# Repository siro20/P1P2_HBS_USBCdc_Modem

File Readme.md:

# Daikin P1/P2 Raspberry Pi hat

This project is about a Raspberry Pi hat/standalone interface to communicate
over the proprietary Daikin P1/P2 power-line bus.

Instead of a [MAX22088](https://www.analog.com/en/products/max22088.html)
it uses a [Raspberry Pi Pico](https://www.raspberrypi.com/products/raspberry-pi-pico/)
and [LM4871](https://www.ti.com/product/LM4871) audio amplifier as modem.

For more details on P1/P2 bus check out
[https://github.com/Arnold-n/P1P2Serial](https://github.com/Arnold-n/P1P2Serial).

It features:
- Galvanic isolation
- 115200baud ASCII [UART interface](pico/doc/uart.md)
- [3 Status LEDs](pico/doc/leds.md)
- Autonomous mode to emulate "External controller" on address F0h
- Bus idle/busy detection
- Collision detection on TX
- Easy to solder: [no QFN parts, only SOIC-8](kicad/doc/circuits.md)
- Cost around 20€ (PCB + parts)
- Raspberry Pi hat compatible (powered from +5V)
- Micro-USB for standalone mode (powered over USB)

The board can be powered over Micro-USB only and doesn't need a Raspberry Pi
baseboard. The communication then will be done over the virtual USB UART.

    This project is not an offical Daikin product. Use own your own risk!
    It has been tested on a Daikin EJHA04AAV3.

## Chapters

- [User handbook](doc/handbook.md)
- [The electronics in detail](kicad/doc/circuits.md)
- [Ti LM4871 vs STM TS4990](kicad/doc/clicks.md)
- [Emulating a differential ADC](pico/doc/ADC.md)
- [Protocol used by the UART](pico/doc/uart.md)
- [Decoding the LED status](pico/doc/leds.md)
- [Hardware off-load the P1/P2 encoding using PIO0](pico/doc/Pio0.md)
- [Hardware off-load inversing ADC channel1](pico/doc/Pio1.md)

## Sources

- The hardware can be found here: [kicad](./kicad)
- The software can be found here: [pico](./pico)
- The host software can be found here: [siro20/P1P2decoder](https://github.com/siro20/P1P2decoder)

## The hardware

There are 3 connectors on the Pi hat:
1. Rasperry Pi 40-pin header
   - Provides power
   - Connects to the UART on GPIO14/GPIO15
   - Connects CTS/RTS on GPIO16/GPIO17
   - Signals a bus collision on GPIO22
2. P1/P2 bus connector
   - P1
   - P2
   - Earth
3. Micro USB
   - Allows to update the Pico firmware
   - Powers the board when used in standalone mode
   - Optional when using the 40-pin header

Buttons:
   - A. Reset button
   - B. Boot-mode button

      Hold button B and press button A to enter the Raspberry Pico USB bootloader.

## Disclaimer

    THE OPEN SOURCE SOFTWARE/HARDWARE IN THIS PROJECT IS DISTRIBUTED
    IN THE HOPE THAT IT WILL BE USEFUL, BUT WITHOUT ANY WARRANTY, WITHOUT
    EVEN THE IMPLIED WARRANTY OF MERCHANTABILITY OR FITNESS FOR A
    PARTICULAR PURPOSE.

    The "Daikin P1/P2 Raspberry Pi hat" has been designed and tested with
    Daikin's P1/P2 bus. You must not use this project to interface any
    other electrical bus.

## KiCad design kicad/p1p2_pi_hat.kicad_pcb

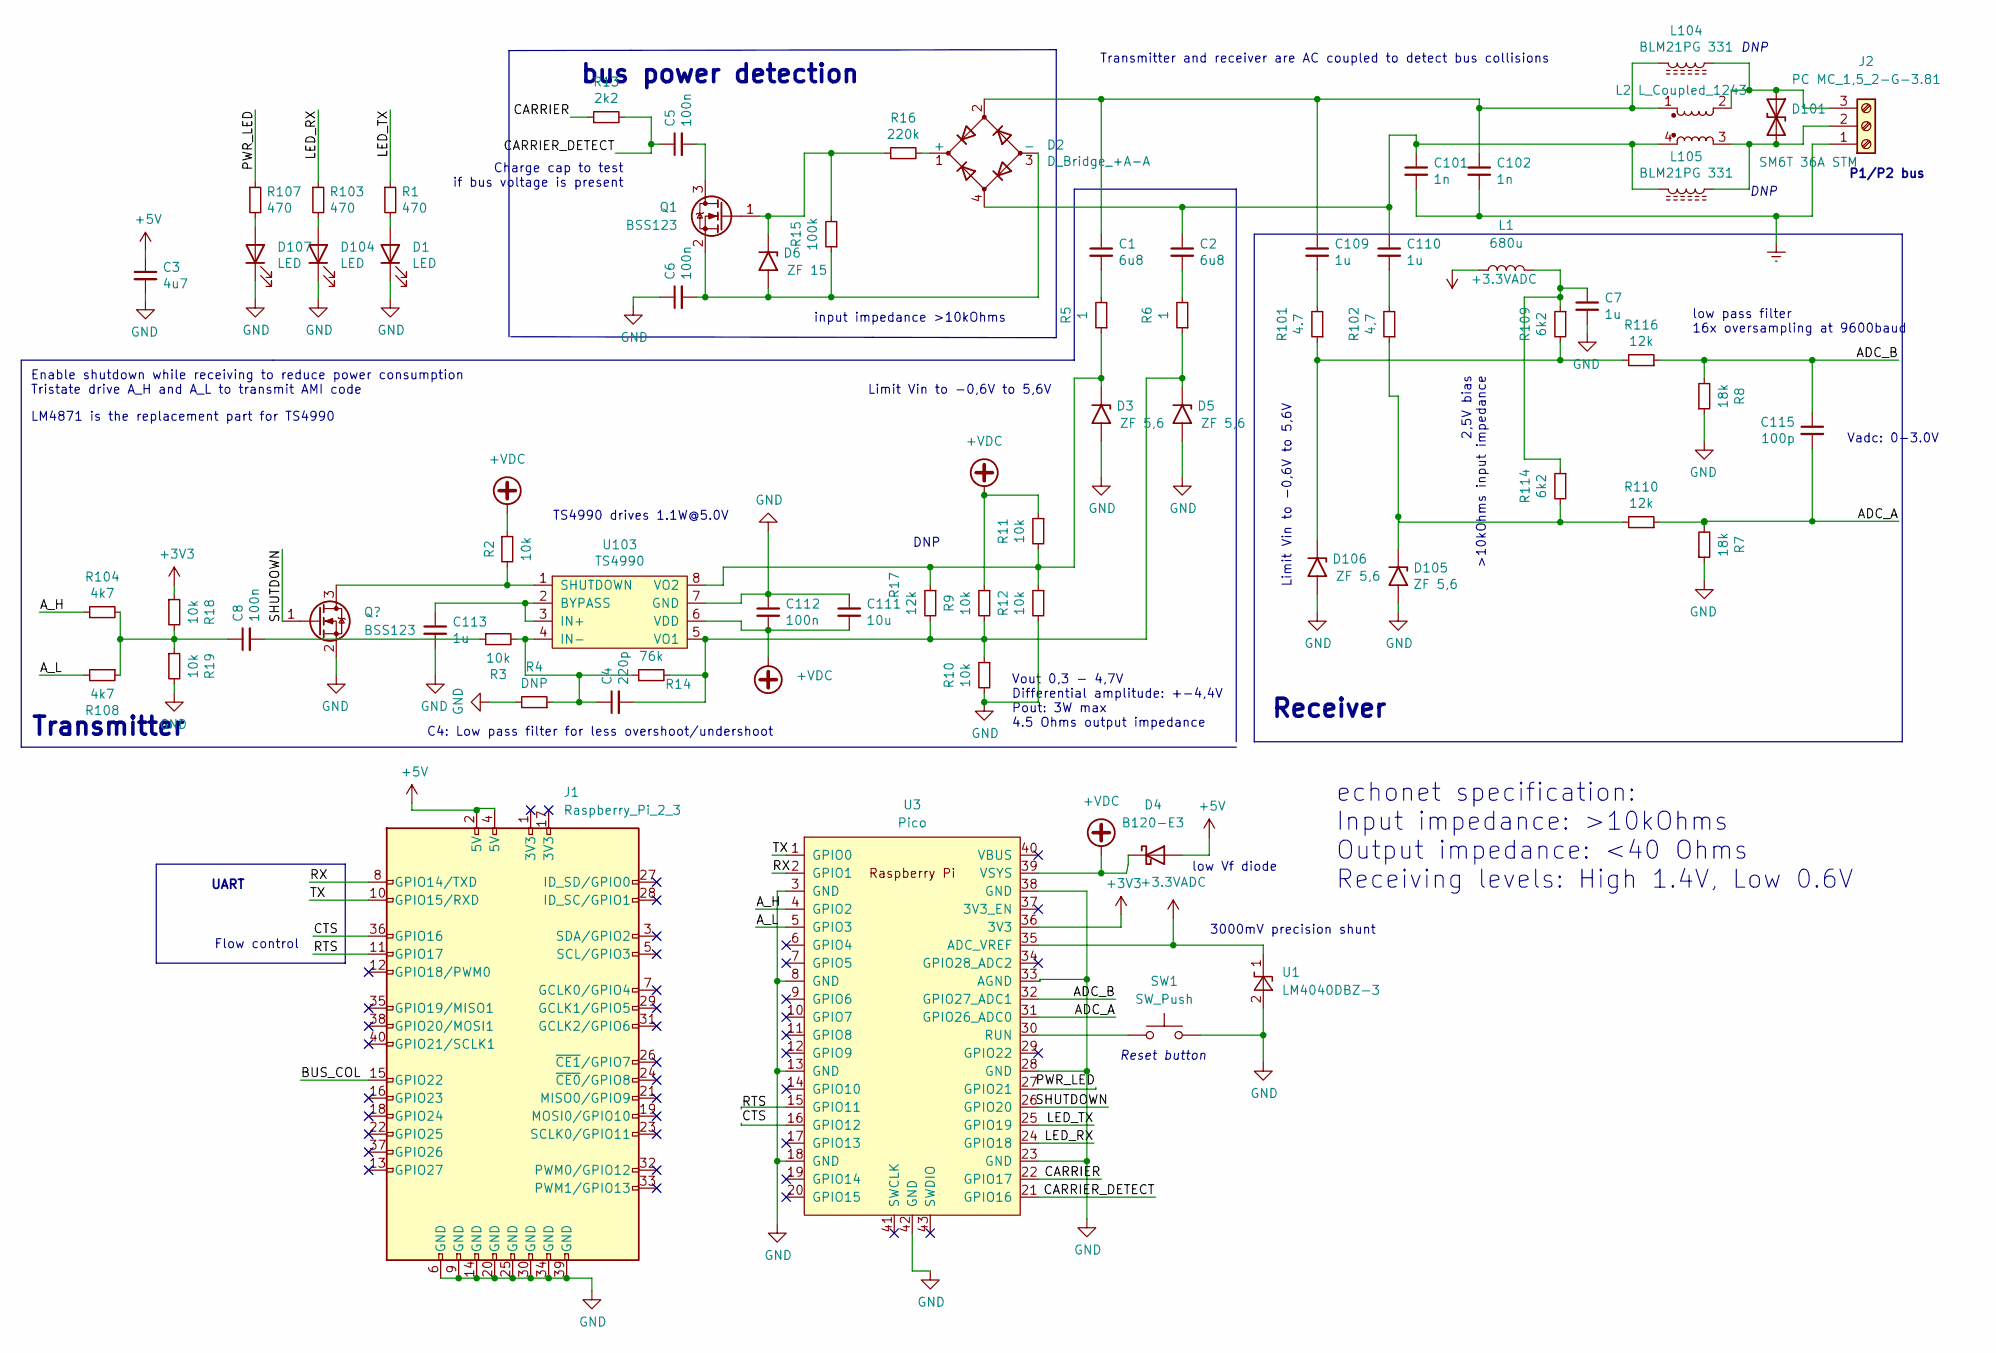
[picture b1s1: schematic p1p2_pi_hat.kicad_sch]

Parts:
C1, C2: 6u8; C_1210_3225Metric_Pad1.33x2.70mm_HandSolder
C3: 4u7; C_1210_3225Metric_Pad1.33x2.70mm_HandSolder
C4: 220p; C_0805_2012Metric_Pad1.18x1.45mm_HandSolder
C5, C6, C8, C112: 100n; C_0805_2012Metric_Pad1.18x1.45mm_HandSolder
C7, C109, C110: 1u; C_1210_3225Metric_Pad1.33x2.70mm_HandSolder
C101, C102: 1n; C_0603_1608Metric_Pad1.08x0.95mm_HandSolder
C111: 10u; C_1210_3225Metric_Pad1.33x2.70mm_HandSolder
C113: 1u; C_0603_1608Metric_Pad1.08x0.95mm_HandSolder
C115: 100p; C_0603_1608Metric_Pad1.08x0.95mm_HandSolder
D1, D104, D107: LED; LED_0805_2012Metric_Pad1.15x1.40mm_HandSolder
D2: D_Bridge_+A-A; Diode_Bridge_Round_D9.0mm
D3, D5, D105, D106: ZF 5,6; D_DO-41_SOD81_P5.08mm_Vertical_AnodeUp
D4: B120-E3; D_SMA
D6: ZF 15; D_DO-41_SOD81_P5.08mm_Vertical_AnodeUp
D101: SM6T 36A STM; D_SMB
J1: Raspberry_Pi_2_3; PinHeader_2x20_P2.54mm_Vertical
J2: PC MC_1,5_2-G-3.81; PhoenixContact_MC_1,5_3-G-3.81_1x03_P3.81mm_Horizontal
L1: 680u; L_1210_3225Metric_Pad1.42x2.65mm_HandSolder
L2: L_Coupled_1243; L_CommonMode_TDK_B82790C0
L104, L105: BLM21PG 331; L_0805_2012Metric_Pad1.15x1.40mm_HandSolder
Q1: BSS123; SOT-23
R1, R103, R107: 470; R_0805_2012Metric_Pad1.20x1.40mm_HandSolder
R2, R3, R9, R10, R11, R12, R18, R19: 10k; R_0805_2012Metric_Pad1.20x1.40mm_HandSolder
R4: DNP; R_0805_2012Metric_Pad1.20x1.40mm_HandSolder
R5, R6: 1; R_0805_2012Metric_Pad1.20x1.40mm_HandSolder
R7, R8: 18k; R_0805_2012Metric_Pad1.20x1.40mm_HandSolder
R13: 2k2; R_0805_2012Metric_Pad1.20x1.40mm_HandSolder
R14: 76k; R_0805_2012Metric_Pad1.20x1.40mm_HandSolder
R15: 100k; R_0805_2012Metric_Pad1.20x1.40mm_HandSolder
R16: 220k; R_0805_2012Metric_Pad1.20x1.40mm_HandSolder
R17, R110, R116: 12k; R_0805_2012Metric_Pad1.20x1.40mm_HandSolder
R101: 4.7; R_0805_2012Metric_Pad1.20x1.40mm_HandSolder
R102: 4,7; R_0805_2012Metric_Pad1.20x1.40mm_HandSolder
R104, R108: 4k7; R_0805_2012Metric_Pad1.20x1.40mm_HandSolder
R109, R114: 6k2; R_0805_2012Metric_Pad1.20x1.40mm_HandSolder
SW1: SW_Push; SW_PUSH_6mm_H5mm
U1: LM4040DBZ-3; SOT-23
U3: Pico; RPi_Pico_SMD_TH
U103: TS4990; SOIC-8_3.9x4.9mm_P1.27mm

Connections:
+3.3VADC: L1.1, U1.1 (K), U3.35 (ADC_VREF)
+3V3: R18.1, U3.36 (3V3)
+5V: C3.1, D4.2 (A), J1.2 (5V), J1.4 (5V)
+VDC: C111.2, C112.2, D4.1 (K), R2.1, R9.1, R11.1, U3.39 (VSYS), U103.6 (VDD)
/ADC_A: C115.2, R7.2, R110.1, U3.31 (GPIO26_ADC0)
/ADC_B: C115.1, R8.2, R116.1, U3.32 (GPIO27_ADC1)
/A_H: R104.1, U3.4 (GPIO2)
/A_L: R108.2, U3.5 (GPIO3)
/BUS_COL: J1.15 (GPIO22)
/CARRIER: R13.1, U3.22 (GPIO17)
/CARRIER_DETECT: C5.1, R13.2, U3.21 (GPIO16)
/CTS: J1.36 (GPIO16), U3.16 (GPIO12)
/LED_RX: R103.1, U3.24 (GPIO18)
/LED_TX: R1.1, U3.25 (GPIO19)
/PWR_LED: R107.1, U3.27 (GPIO21)
/RTS: J1.11 (GPIO17), U3.15 (GPIO11)
/RX: J1.8 (GPIO14/TXD), U3.2 (GPIO1)
/SHUTDOWN: U3.26 (GPIO20); also elsewhere on the board
/TX: J1.10 (GPIO15/RXD), U3.1 (GPIO0)
Earth: C101.2, C102.2, J2.1
GND: C3.2, C6.1, C7.2, C111.1, C112.1, C113.2, D1.1 (K), D3.2 (A2), D5.2 (A2), D104.1 (K), D105.2 (A2), D106.2 (A2), D107.1 (K), J1.6 (GND), J1.9 (GND), J1.14 (GND), J1.20 (GND), J1.25 (GND), J1.30 (GND), J1.34 (GND), J1.39 (GND), R4.2, R7.1, R8.1, R10.2, R12.2, R19.2, SW1.2, U1.2 (A), U3.3 (GND), U3.8 (GND), U3.13 (GND), U3.18 (GND), U3.23 (GND), U3.28 (GND), U3.33 (AGND), U3.38 (GND), U3.42 (GND), U103.7 (GND); also elsewhere on the board
unnamed: C1.1, C102.1, C109.1, D2.2, L2.1, L104.2
unnamed: C1.2, R5.2
unnamed: C2.2, R6.2
unnamed: C4.1, R3.2, R4.1, R14.1, U103.4 (IN-)
unnamed: C4.2, D5.1 (A1), R6.1, R9.2, R10.1, R14.2, R17.2, U103.5 (VO1)
unnamed: C5.2, Q1.3 (D)
unnamed: C6.2, D2.3 (-), D6.2 (A2), Q1.2 (S), R15.1
unnamed: C7.1, L1.2, R109.1, R114.1
unnamed: C8.1, R18.2, R19.1, R104.2, R108.1
unnamed: C8.2, R3.1
unnamed: C2.1, C101.1, C110.1, D2.4, L2.4, L105.2
unnamed: C109.2, R101.2
unnamed: C110.2, R102.2
unnamed: C113.1, U103.2 (BYPASS), U103.3 (IN+)
unnamed: D1.2 (A), R1.2
unnamed: D2.1 (+), R16.2
unnamed: D3.1 (A1), R5.1, R11.2, R12.1, R17.1, U103.8 (VO2)
unnamed: D6.1 (A1), Q1.1 (G), R15.2, R16.1
unnamed: D101.1 (A1), J2.3, L2.2, L104.1
unnamed: D101.2 (A2), J2.2, L2.3, L105.1
unnamed: D104.2 (A), R103.2
unnamed: D105.1 (A1), R102.1, R110.2, R114.2
unnamed: D106.1 (A1), R101.1, R109.2, R116.2
unnamed: D107.2 (A), R107.2
unnamed 45: R2.2, U103.1 (SHUTDOWN); also elsewhere on the board
unnamed: SW1.1, U3.30 (RUN)

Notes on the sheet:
P1/P2 bus
bus power detection
TS4990 drives 1.1W@5.0V
DNP
UART
Transmitter and receiver are AC coupled to detect bus collisions
C4: Low pass filter for less overshoot/undershoot
input impedance >10kOhms
Vout 0,3 - 4,7V Differential amplitude: +-4,4V Pout: 3W max 4.5 Ohms output impedance
low Vf diode
low pass filter 16x oversampling at 9600baud
Reset button
Flow control
Limit Vin to -0,6V to 5,6V
Transmitter
echonet specification: Input impedance: >10kOhms Output impedance: <40 Ohms Receiving levels: High 1.4V, Low 0.6V
Charge cap to test if bus voltage is present
3000mV precision shunt
2,5V bias >10kOhms input impedance
Enable shutdown while receiving to reduce power consumption Tristate drive A_H and A_L to transmit AMI code
Vadc: 0-3.0V
LM4871 is the replacement part for TS4990
Receiver

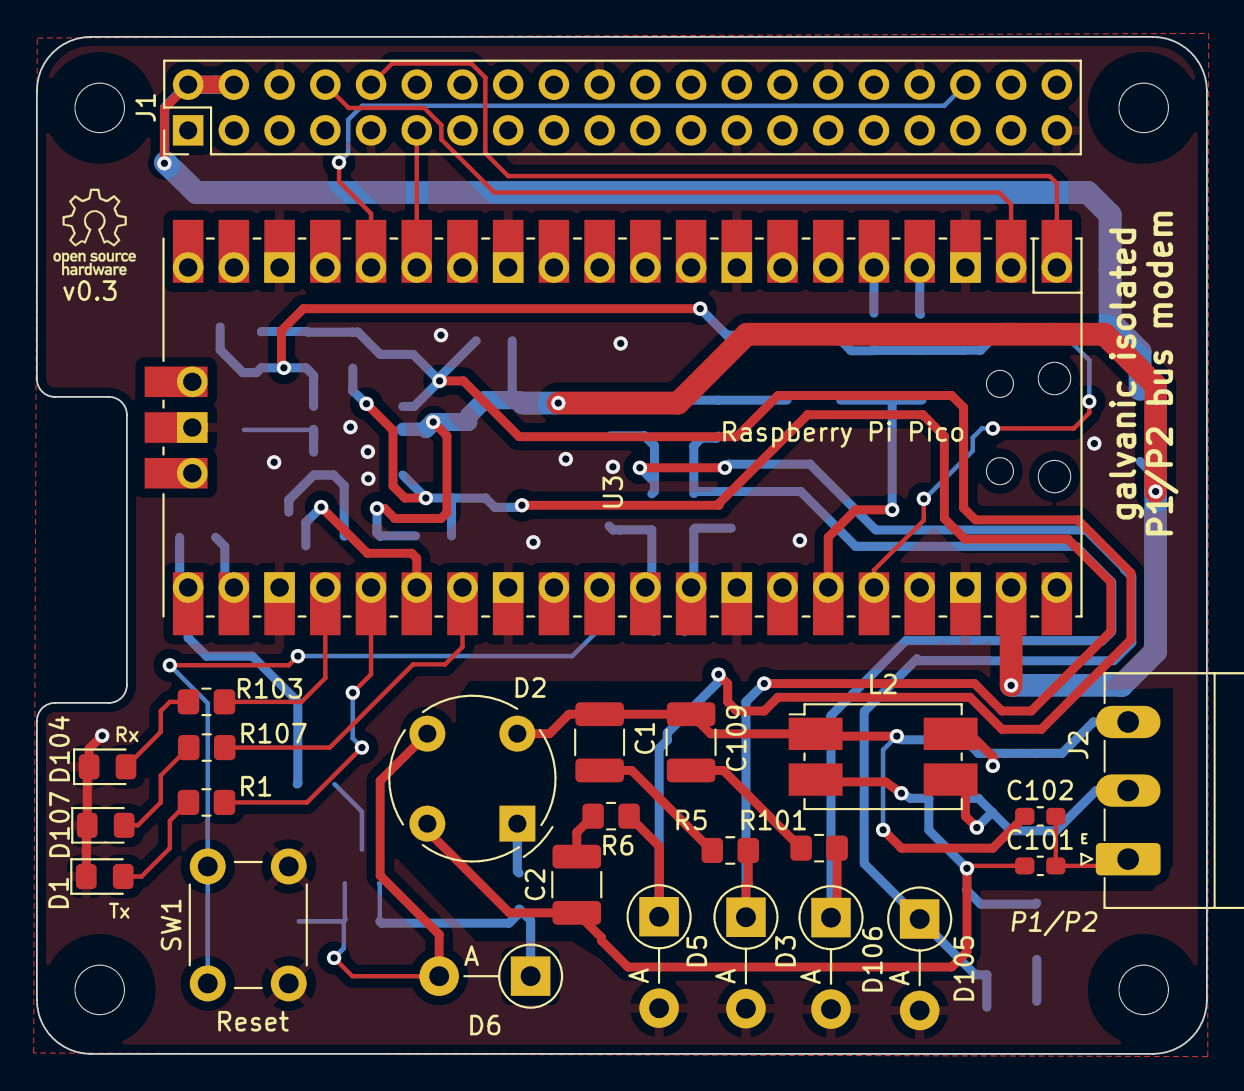
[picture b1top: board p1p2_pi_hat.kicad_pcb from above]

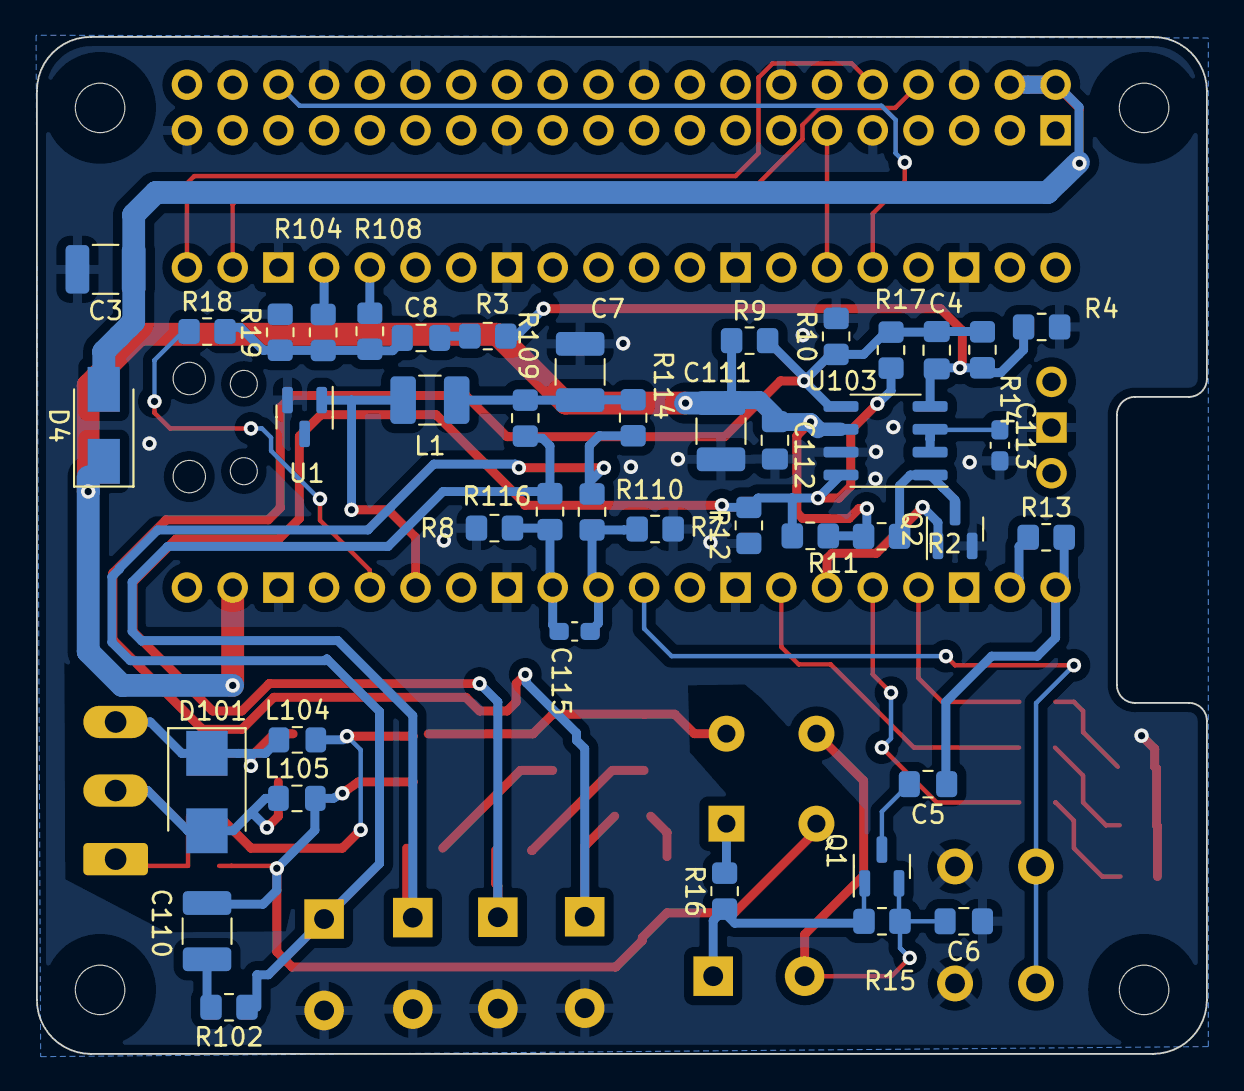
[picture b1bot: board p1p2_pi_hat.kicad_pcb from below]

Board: 2 copper layers, 65.0 x 56.5 mm, 68 parts (43 on the bottom side), 46 nets.

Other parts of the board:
Q2: BSS123; SOT-23

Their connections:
/SHUTDOWN: Q2.1 (G); also elsewhere on the board
GND: Q2.2 (S); also elsewhere on the board
unnamed 45: Q2.3 (D); also elsewhere on the board

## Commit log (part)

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2021-09-04 Initial commit
    - Add schematics and PCB
    - Still WIP
2021-09-07 Update PCB
    - Increase dimension for easy DIN rail mounting
    - Add more labels
    - Move parts to increase ground plane
2021-09-07 Add 9600baud CTS low pass filter
    - Add low pass filter with tRC of 1.2 msec
    - Pull CTS low when data is received for easy collision detection
2021-09-18 Update PCB
2021-09-18 Add PDF/PNG showing 3D view, schematics and PCB
2021-09-22 pcb: Place Arduino on board
    Add an Arduino to the board and a connector for external microcontrollers.
    The HBS protocol requires AMI code to be transmitted, which cannot be easily
    be done in hardware due to clock recovery issues.
2021-10-01 Fix some issues
    - Fix Q101 pinout
    - Change 2k5 to 2k49 Ohm
    - Change 720 to 750 Ohm
2022-01-02 pcb: Convert to standalone AMI AFE
2022-06-03 kicad: Create a PI hat compatible P1/P2 modem
    Create a P1/P2 transceiver as Rapsberry PI hat using some
    analog components and a Raspberry PI Pico (RP2040).
2022-06-04 kicad: Minor fixes
2022-06-30 submodules: Add pico-sdk
2022-09-06 Add RPI pico source code
    Use ADC, DMA, PIO0, PIO1 and lot's of optimised C++ to create a P1/P2 modem.
    TODO:
    - Host interface
    - Documentation
2022-11-05 kicad: Update schematics
    - Add common mode choke
    - Use gain 5 for OpAmp
    The OpAmp is not stable at unity gain.
    The OpAmp is not stable with high impedance load (unconnected P1/P2 bus).
    - Use OpAmp in inverting operation mode instead voltage follower mode
    - Add 'DNP' pull down and capacitor on OpAmp feedback
2022-11-05 tests: Rename main.cpp
2022-11-05 uart_pio: Return error on FIFO overrun
2022-11-05 src: Use 32bit memory access
    16bit access is slow on Cortex-M0, use 32bit access for faster code.
2022-11-05 src: Add DC blocker
2022-11-05 Code cleanup
2022-11-05 twos_complement: Add IRQ support
    Trigger an IRQ when FIFO is not empty. This allows to use __wfe().
    The DMA channel would be a even better, but it does not trigger an
    IRQ on finished transfer chunk.
2022-11-05 led_driver: Synchronize LEDs
2022-11-05 level_detect: Add hysteresis and reduce signal level on line idle
    This improves the signal quality as the AC coupling introduces distortions.
2022-11-05 uart: Move probabilty decision into uart_bit_detect
    Move the decision if a symbol is +1, -1 or idle to uart_bit_detect.
2022-11-05 defines.hpp: Add define for external resistor divider
    Introduce ADC_EXTERNAL_GAIN to compensate external resistor divider.
    Remove hardcoded value from main.
2022-11-05 src/uart: Move UARTbit to main
2022-11-05 src/uart: Use only one shift register
2022-11-05 src: Remove code from scratch_x and scratch_y SRAM space
    Only place data in sratch_x and sratch_y SRAM space.
2022-11-05 Add documentation
2022-11-05 kicad: Update schematic
2022-11-05 uart_pio: Add support for sending messages
2022-11-05 twos_complement: Make functions return void
    This fixes a crash where GCC emitted invalid code.
2022-11-05 src/adc: Drop hardware/interp
    It's unused.
2022-11-05 uart: Fix spacing
2022-11-05 main: Properly data between cores
    The Core0 now informs Core1 about a busy and a free bus. This
    can be used to implement the half duplex sending/receiving
    statemachine on Core1.
2022-11-05 main: Multiple fixes
    - Implement TX state machine
    Block the transmission of packets until the line is free.
    - Use STDIO methods to transceive data over UART0 and USB CDC.
    - Fix Message c_str function
2022-11-05 pico: Add missing LED manager header
2022-11-05 .gitignore: Update file
2022-11-06 pico: Add missing header
2022-11-06 pico/tests: Fix message unit tests
2022-11-06 pico/src: Drop gain
    It's unused.
2022-11-06 main.cpp: Drop testing and now unused code
2022-11-06 pico/src/main: Put LM4861 into sleep
    Drive the lines only when transmitting.
2022-11-06 pico/src/main: Move printf and sleep to core0
    This fixes core0 not being able to send data to core1 for
    3 seconds.
2022-11-06 pico/src: Remove unused variable
2022-11-06 pico/src/main: Drain fifo on core1 entry
2022-11-06 pico/tests/uart_bit_detect: Fix unit test
2022-11-06 pico/src/main: Clear Core1Data on error path as well
2022-11-06 pico/src: Drop channel_comp
    It's unused.
2022-11-20 main: Move code
2022-11-20 main: Switch core0 and core1
    stdio_init_all() must be called on core0.
    Move UART handling code to core0 and ADC code to core1.
2022-11-20 main: Prefix welcome banner
2022-11-23 pico: Replace IRQ fifo
    Drop circular_buffer_spinlock and line_receiver and replace
    it with an IRQ safe FIFO. As data doesn't need to be transfered
    between cores, there's no need for a spinlock.
2022-11-26 main: Update TX handling
    - Add timeout for TX buffer enables (15 milliseconds)
    - Add line busy timeout
    - Enable WFE with timeout
    - Disable TX buffer by default to make line high impedance
2022-11-26 Update documenation
2022-11-26 main: Rename DAC to DADC
2022-11-27 Documentation: Add LED chapter
2022-11-27 kicad: Add warning texts to design
2022-12-17 doc: Explain RPi3 UART0 pitfalls
2022-12-31 main: Signal FifoErr to host
2022-12-31 pico/src/adc: Fix DMA block IRQ handler
    Need to reset the write address register, as it's not the start
    address register, but the actual target write address register
    incrementing on each transfer.
    Clear the DMA IRQ and don't reset DMA inside the IRQ handler.
    Move resetting the DMA to Update() method to prevent race conditions
    with IRQ handler.
2023-01-04 pico/src/uart_pio: Add more comments
2023-01-04 src/uart_pio: Fix SW to HW FIFO IRQ handler
    Prevent race conditions filling the HW FIFO.
    Only fill the SW FIFO and let the IRQ handler fill
    the HW FIFO to prevent glitches when HW FIFO has
    been filled with 8 bytes.
2023-01-04 pico/src: Add Daikin external controller emulation
    Answer request on address 0xF0 to emulate Daikin external
    controller. Scan the bus to prevent address collisions
    with existing controllers on 0xF0 or 0xF1.
    Tested using Daiking P1P2 bus. The main controller is able
    to see the response and adds additional packets on the bus.
2023-01-06 standalone: Use absolute_time_t instead of size_t
    Fixes standalone not working after serveral hours.
2023-01-06 pico: Update uart documentation
2023-01-07 Update Readme.md: Add build instruction
    Explain how to build the Pico source code.
2023-01-07 pico/tests: Make FIR filter less verbose
    Remove verbose prints and check frequency response.
2023-01-09 pico/tests: Add test for FIFO
2023-01-09 pico/src/standalone: Answer packet 00f031
    Anser the request and return the expected DeviceID.
    This fixes 'installer mode' cannot be entered on the control unit.
2023-01-09 pico/src/main: Send PIO overrun to host
    Do not only blink the LED but also send the PIO overrun to the
    host and flush the queue.
2023-01-09 pico/src/host_uart: Allow to enter USB bootloader
    On received string ";!BLD!;" enter the USB bootloader.
2023-01-10 pico: Add line_receiver_irqsafe
    For host uart receival add line_receiver_irqsafe as new
    class. Optimize fifo_irqsafe to be faster, but incompatible
    with host uart receival.
2023-01-10 pico/src/uart_pio: Use DMA instead of IRQ
    Replace software FIFO with IRQ support with DMA fifo.
    Reduces CPU load on transmitting data using UART PIO.
2023-01-10 pico/src/main: Handle more errors in TX state machine
2023-01-14 pico/src/uart: Drop outdated comment
2023-01-21 Update Readme
    Add more features.
2023-01-21 pico/src/standalone: Request all data packets
2023-01-21 pico/tests: Add test for empty message
2023-01-21 kicad/doc: Update documentation
    - Recommend LM4871 instead LM4861
    - Add experimental results
2023-01-21 pico/src/uart: Add method to print shiftreg contents
2023-01-21 pico/src/host_uart: Improve string parsing
    - Ignore messages with no data.
    - Don't parse messages starting with CR or LF
2023-01-21 pico/src/main: Don't overwrite status if already set
2023-01-21 kicad: Update schematics
2023-04-02 kicad: Redesign to TX with more power
    - Use 5V as LM4871 power supply
    - Decrease output impedance to 4.5 Ohms
    - Decrease input impedance to 1k Ohm
    - AC couple input signal
2023-07-03 main: Add timeout for TX state machine
    Make sure to abort TX on timeout.
2023-07-03 kicad: Fixes for version v0.3
    - Replace Ti LM4871 with STM TS4990
    - Power SHUTDOWN from +5V rail
    - Use double ground plane
2023-08-25 pico/main: On RxError add received char to message
    Add all received characters to RxMessage.
2023-08-25 pico/src/main: Remove stray semikolon
2023-08-25 pico/src/main: Add comment and improve code
2023-08-25 pico/defines: TS4990 has longer startup time
    TS4990 has a startup time of 32 msec.
2023-08-25 pico: Fix shutdown level
    Since v0.3 the shutdown polarity is inverted.
2023-08-25 doc: Add v0.3 pictures
2023-08-26 kicad/doc: Add startup time
    Add startup time of STM TS4990.
2024-10-02 kicad: Update pictures
2024-10-02 kicad: Rename kicad files
2024-10-02 kicad: use DNP flag
2024-10-02 Readme: minor fixes
2025-05-17 uart_bit_detect_fast: Fix typo
2025-05-17 uart_bit_detect_fast: Reduce code size
2025-05-17 shiftreg.hpp: Generate smaller code
    Optimize the code to generate less assembly instructions.
2025-05-17 pico: Bump pico-sdk to 2.1.0
    Adapt the code to compile with new SDK.
2025-05-17 .gitignore: Add generated files
2025-05-17 CMakeLists: Add comment explaining using newlib-nano
2025-05-17 uart_bit_detect_fast.hpp: Fix comment
    The function returns void, so fix the comment.
2025-05-17 message: Drop time and move status to the end
    Reformat the message to send the hex-data first and make the status
    optional. It's only send if non zero and separated by #.
    The parser is allowed to drop anything after char '#' or ','.
2025-05-18 CMakeLists: Fix linking
2025-05-18 tests: Add missing files for tx_statemachine_test
    Mock the PIO and the timebase.
2025-05-18 src: Add adc_sw
    Add software implementation of differential ADC. Uses IRQ
    safe FIFO and interrupts instead of DMA + PIO + DMA.
2025-05-18 adc_sw: Use round_robin mode
2025-05-18 adc: Fix IRQ registered on wrong core
    This caused the core to not wake often enough causing a buffer underflow.
    That in turn causes peaks in the signal as the inverting and non-inverting
    channel might get flipped.
    Now the the correct core registers the IRQ handler the correct core is also
    woken up on IRQ and can process the data.
2025-05-18 main: Use DMA differential ADC
    The IRQ based solution isn't fast enough for 16x oversampling.
    Use the DMA based differential ADC, it's faster.
2025-05-18 adc_sw: Improve code
    Make it simpler and use bigger SW FIFO.
2025-05-18 doc: Update UART
    Describe new format being used.
2025-05-30 standalone: Cache type 3xh packets
    Cache type 3xh packets and send as response to the bus master
    once it's requesting an answer from the external controller.
    TEST: Can change parameter 35h on Daikin system.
2025-06-06 standalone: Request handling of 0x3xh packets
    In the response of 30h packets acknowledge which other 3xh packets
    are currently pending and require transmission.
2025-06-15 pico: Improvements around TX packets
    - Always answer 3xh packets. This reduce the time spent waiting
    for the next 3xh packet.
    - Improve host uart parsing
    - Transmit regular packets at the end of 3xh packet phase, by appending
    it to the statemachine when the output driver is still active.
    This allows to send the packet earlier (no need to wait for the output
2025-06-16 pico/standalone: Code optimization
